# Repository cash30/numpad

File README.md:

<p><b style="font-weight:normal;" id="docs-internal-guid-06ec4c6b-7fff-9c5e-59c2-9c24a0eed1a2"><p dir="ltr" style="line-height:1.425;text-align: center;margin-top:12pt;margin-bottom:12pt;"><span style="font-size:12pt;font-family:Verdana,sans-serif;color:#333333;background-color:#ffffff;font-weight:700;font-style:normal;font-variant:normal;text-decoration:none;vertical-align:baseline;white-space:pre;white-space:pre-wrap;">My Hackpad is just a numpad I'm going to use with the laptop I got from Siege. It's going to have 9 buttons and a rotary encoder for volume.&nbsp;</span></p><p dir="ltr" style="line-height:1.425;text-align: center;margin-top:12pt;margin-bottom:12pt;"><span style="font-size:12pt;font-family:Verdana,sans-serif;color:#333333;background-color:#ffffff;font-weight:700;font-style:normal;font-variant:normal;text-decoration:none;vertical-align:baseline;white-space:pre;white-space:pre-wrap;">Below are pictures of the CAD, schematic, and PCB layout.</span><span style="font-size:12pt;font-family:Verdana,sans-serif;color:#333333;background-color:#ffffff;font-weight:700;font-style:normal;font-variant:normal;text-decoration:none;vertical-align:baseline;white-space:pre;white-space:pre-wrap;"><br></span><span style="font-size:12pt;font-family:Verdana,sans-serif;color:#333333;background-color:#ffffff;font-weight:700;font-style:normal;font-variant:normal;text-decoration:none;vertical-align:baseline;white-space:pre;white-space:pre-wrap;"><br></span><span style="font-size:12pt;font-family:Verdana,sans-serif;color:#333333;background-color:#ffffff;font-weight:700;font-style:normal;font-variant:normal;text-decoration:none;vertical-align:baseline;white-space:pre;white-space:pre-wrap;">I've never made a PCB before so that was neat and i got to actually use CAD for something useful!</span><span style="font-size:12pt;font-family:Verdana,sans-serif;color:#333333;background-color:#ffffff;font-weight:700;font-style:normal;font-variant:normal;text-decoration:none;vertical-align:baseline;white-space:pre;white-space:pre-wrap;"><br></span><span style="font-size:12pt;font-family:Verdana,sans-serif;color:#333333;background-color:#ffffff;font-weight:700;font-style:normal;font-variant:normal;text-decoration:none;vertical-align:baseline;white-space:pre;white-space:pre-wrap;">&nbsp;</span></p><p dir="ltr" style="line-height:1.38;text-align: center;margin-top:0pt;margin-bottom:0pt;"><span style="font-size:12pt;font-family:Verdana,sans-serif;color:#333333;background-color:#ffffff;font-weight:700;font-style:normal;font-variant:normal;text-decoration:none;vertical-align:baseline;white-space:pre;white-space:pre-wrap;"><span style="border:none;display:inline-block;overflow:hidden;width:800px;height:644px;">

<p><strong style="font-weight:normal;" id="docs-internal-guid-06ec4c6b-7fff-9c5e-59c2-9c24a0eed1a2"><span style="font-size:12pt;font-family:Verdana,sans-serif;color:#333333;background-color:#ffffff;font-weight:700;font-style:normal;font-variant:normal;text-decoration:none;vertical-align:baseline;white-space:pre;white-space:pre-wrap;"></span><br></strong></p><p dir="ltr" style="line-height:1.425;text-align: center;margin-top:12pt;margin-bottom:12pt;"><strong style="font-weight:normal;" id="docs-internal-guid-06ec4c6b-7fff-9c5e-59c2-9c24a0eed1a2"><span style="font-size:12pt;font-family:Verdana,sans-serif;color:#333333;background-color:#ffffff;font-weight:700;font-style:normal;font-variant:normal;text-decoration:none;vertical-align:baseline;white-space:pre;white-space:pre-wrap;">BOM:</span></strong></p><ul style="margin-top:0;margin-bottom:0;padding-inline-start:48px;"><li dir="ltr" style="list-style-type:disc;font-size:12pt;font-family:Verdana,sans-serif;color:#333333;background-color:transparent;font-weight:700;font-style:normal;font-variant:normal;text-decoration:none;vertical-align:baseline;white-space:pre;" aria-level="1"><p dir="ltr" style="line-height:1.425;margin-top:12pt;margin-bottom:0pt;" role="presentation"><strong style="font-weight:normal;" id="docs-internal-guid-06ec4c6b-7fff-9c5e-59c2-9c24a0eed1a2"><span style="font-size:12pt;font-family:Verdana,sans-serif;color:#333333;background-color:#ffffff;font-weight:700;font-style:normal;font-variant:normal;text-decoration:none;vertical-align:baseline;white-space:pre;white-space:pre-wrap;">9x Cherry MX red switches</span></strong></p></li><li dir="ltr" style="list-style-type:disc;font-size:12pt;font-family:Verdana,sans-serif;color:#333333;background-color:transparent;font-weight:700;font-style:normal;font-variant:normal;text-decoration:none;vertical-align:baseline;white-space:pre;" aria-level="1"><p dir="ltr" style="line-height:1.425;margin-top:0pt;margin-bottom:0pt;" role="presentation"><strong style="font-weight:normal;" id="docs-internal-guid-06ec4c6b-7fff-9c5e-59c2-9c24a0eed1a2"><span style="font-size:12pt;font-family:Verdana,sans-serif;color:#333333;background-color:#ffffff;font-weight:700;font-style:normal;font-variant:normal;text-decoration:none;vertical-align:baseline;white-space:pre;white-space:pre-wrap;">1x XIAO RP2040</span></strong></p></li><li dir="ltr" style="list-style-type:disc;font-size:12pt;font-family:Verdana,sans-serif;color:#333333;background-color:transparent;font-weight:700;font-style:normal;font-variant:normal;text-decoration:none;vertical-align:baseline;white-space:pre;" aria-level="1"><p dir="ltr" style="line-height:1.425;margin-top:0pt;margin-bottom:0pt;" role="presentation"><strong style="font-weight:normal;" id="docs-internal-guid-06ec4c6b-7fff-9c5e-59c2-9c24a0eed1a2"><span style="font-size:12pt;font-family:Verdana,sans-serif;color:#333333;background-color:#ffffff;font-weight:700;font-style:normal;font-variant:normal;text-decoration:none;vertical-align:baseline;white-space:pre;white-space:pre-wrap;">9x keycaps</span></strong></p></li><li dir="ltr" style="list-style-type:disc;font-size:12pt;font-family:Verdana,sans-serif;color:#333333;background-color:transparent;font-weight:700;font-style:normal;font-variant:normal;text-decoration:none;vertical-align:baseline;white-space:pre;" aria-level="1"><p dir="ltr" style="line-height:1.425;margin-top:0pt;margin-bottom:0pt;" role="presentation"><strong style="font-weight:normal;" id="docs-internal-guid-06ec4c6b-7fff-9c5e-59c2-9c24a0eed1a2"><span style="font-size:12pt;font-family:Verdana,sans-serif;color:#333333;background-color:#ffffff;font-weight:700;font-style:normal;font-variant:normal;text-decoration:none;vertical-align:baseline;white-space:pre;white-space:pre-wrap;">1x 2-sided PCB</span></strong></p></li><li dir="ltr" style="list-style-type:disc;font-size:12pt;font-family:Verdana,sans-serif;color:#333333;background-color:transparent;font-weight:700;font-style:normal;font-variant:normal;text-decoration:none;vertical-align:baseline;white-space:pre;" aria-level="1"><p dir="ltr" style="line-height:1.425;margin-top:0pt;margin-bottom:0pt;" role="presentation"><strong style="font-weight:normal;" id="docs-internal-guid-06ec4c6b-7fff-9c5e-59c2-9c24a0eed1a2"><span style="font-size:12pt;font-family:Verdana,sans-serif;color:#333333;background-color:#ffffff;font-weight:700;font-style:normal;font-variant:normal;text-decoration:none;vertical-align:baseline;white-space:pre;white-space:pre-wrap;">full 3D printed case</span></strong></p></li><li dir="ltr" style="list-style-type:disc;font-size:12pt;font-family:Verdana,sans-serif;color:#333333;background-color:transparent;font-weight:700;font-style:normal;font-variant:normal;text-decoration:none;vertical-align:baseline;white-space:pre;" aria-level="1"><p dir="ltr" style="line-height:1.425;margin-top:0pt;margin-bottom:0pt;" role="presentation"><strong style="font-weight:normal;" id="docs-internal-guid-06ec4c6b-7fff-9c5e-59c2-9c24a0eed1a2"><span style="font-size:12pt;font-family:Verdana,sans-serif;color:#333333;background-color:#ffffff;font-weight:700;font-style:normal;font-variant:normal;text-decoration:none;vertical-align:baseline;white-space:pre;white-space:pre-wrap;">4x M3x16 Bolt</span></strong></p></li><li dir="ltr" style="list-style-type:disc;font-size:12pt;font-family:Verdana,sans-serif;color:#333333;background-color:transparent;font-weight:700;font-style:normal;font-variant:normal;text-decoration:none;vertical-align:baseline;white-space:pre;" aria-level="1"><p dir="ltr" style="line-height:1.425;margin-top:0pt;margin-bottom:12pt;" role="presentation"><strong style="font-weight:normal;" id="docs-internal-guid-06ec4c6b-7fff-9c5e-59c2-9c24a0eed1a2"><span style="font-size:12pt;font-family:Verdana,sans-serif;color:#333333;background-color:#ffffff;font-weight:700;font-style:normal;font-variant:normal;text-decoration:none;vertical-align:baseline;white-space:pre;white-space:pre-wrap;">4x M3 Heatset</span></strong></p></li></ul><p><br></p>

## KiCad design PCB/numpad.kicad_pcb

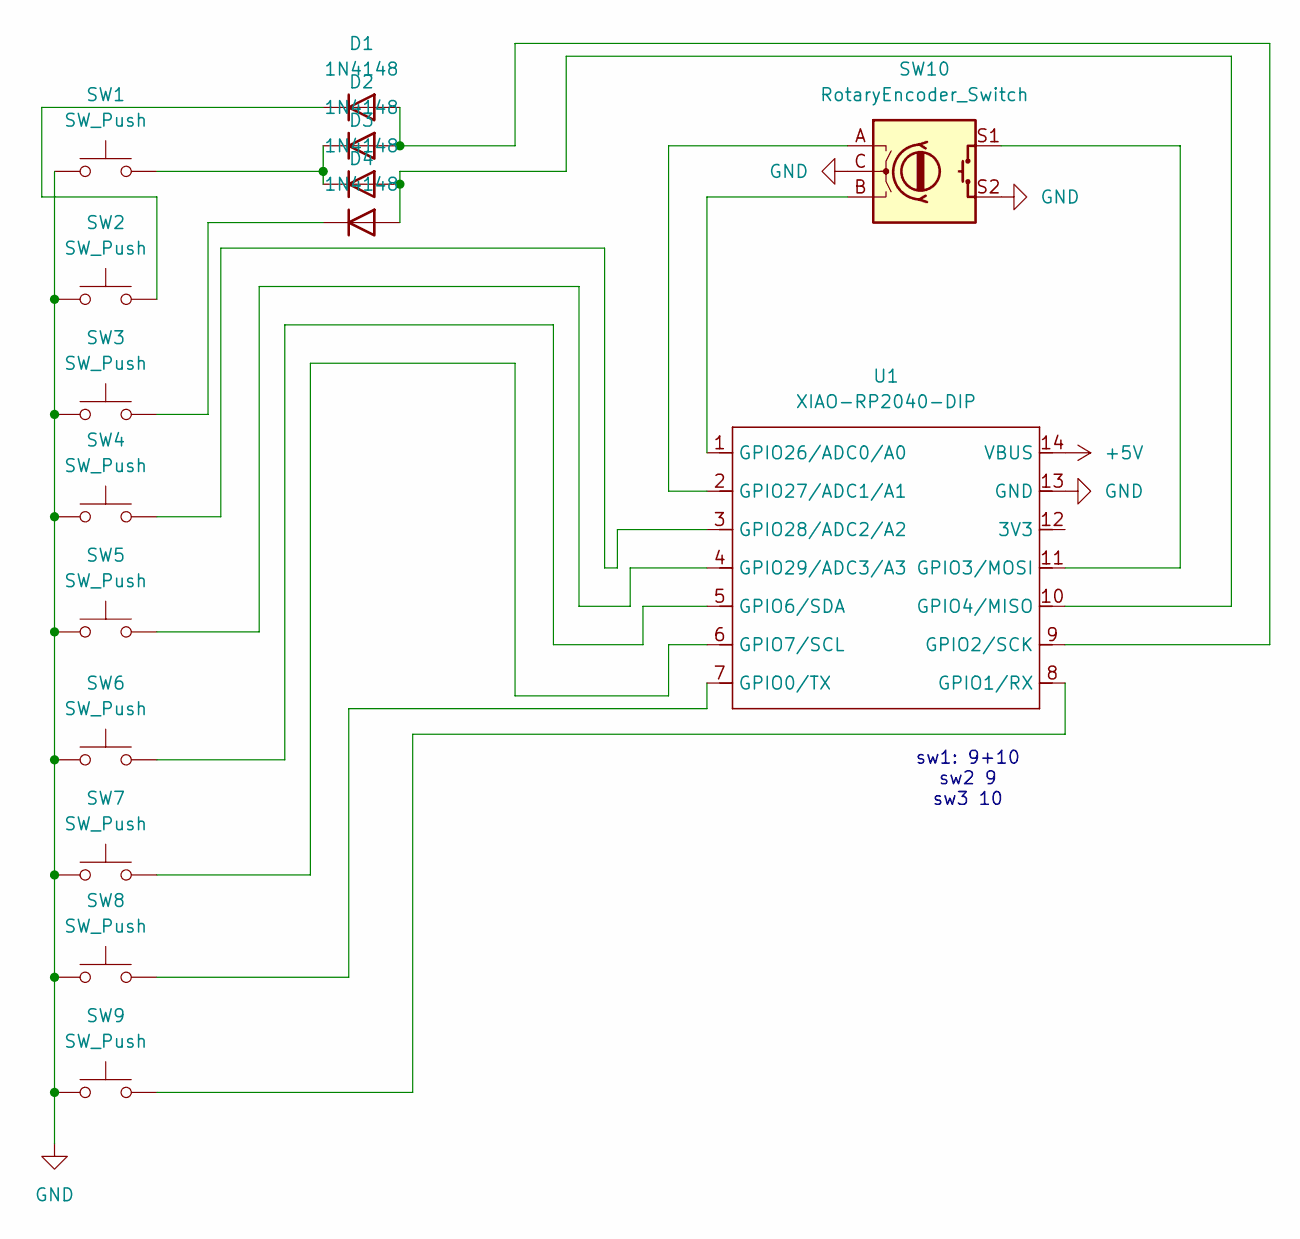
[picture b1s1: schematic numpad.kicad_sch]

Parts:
D1, D2, D3, D4: 1N4148; D_DO-35_SOD27_P7.62mm_Horizontal
SW1, SW2, SW3, SW4, SW5, SW6, SW7, SW8, SW9: SW_Push; SW_Cherry_MX_1.00u_PCB
SW10: RotaryEncoder_Switch; RotaryEncoder_Alps_EC11E-Switch_Vertical_H20mm
U1: XIAO-RP2040-DIP

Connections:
+5V: U1.14 (VBUS)
GND: SW1.1, SW2.1, SW3.1, SW4.1, SW5.1, SW6.1, SW7.1, SW8.1, SW9.1, SW10.C, SW10.S2, U1.13 (GND)
unnamed: D1.2 (A), D2.2 (A), U1.9 (GPIO2/SCK)
unnamed: D1.1 (K), SW2.2
unnamed: D2.1 (K), D3.1 (K), SW1.2
unnamed: D3.2 (A), D4.2 (A), U1.10 (GPIO4/MISO)
unnamed: D4.1 (K), SW3.2
unnamed: SW8.2, U1.7 (GPIO0/TX)
unnamed: SW9.2, U1.8 (GPIO1/RX)
unnamed: SW10.S1, U1.11 (GPIO3/MOSI)
unnamed: SW6.2, U1.5 (GPIO6/SDA)
unnamed: SW7.2, U1.6 (GPIO7/SCL)
unnamed: SW10.B, U1.1 (GPIO26/ADC0/A0)
unnamed: SW10.A, U1.2 (GPIO27/ADC1/A1)
unnamed: SW4.2, U1.3 (GPIO28/ADC2/A2)
unnamed: SW5.2, U1.4 (GPIO29/ADC3/A3)

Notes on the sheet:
sw1: 9+10 sw2 9 sw3 10

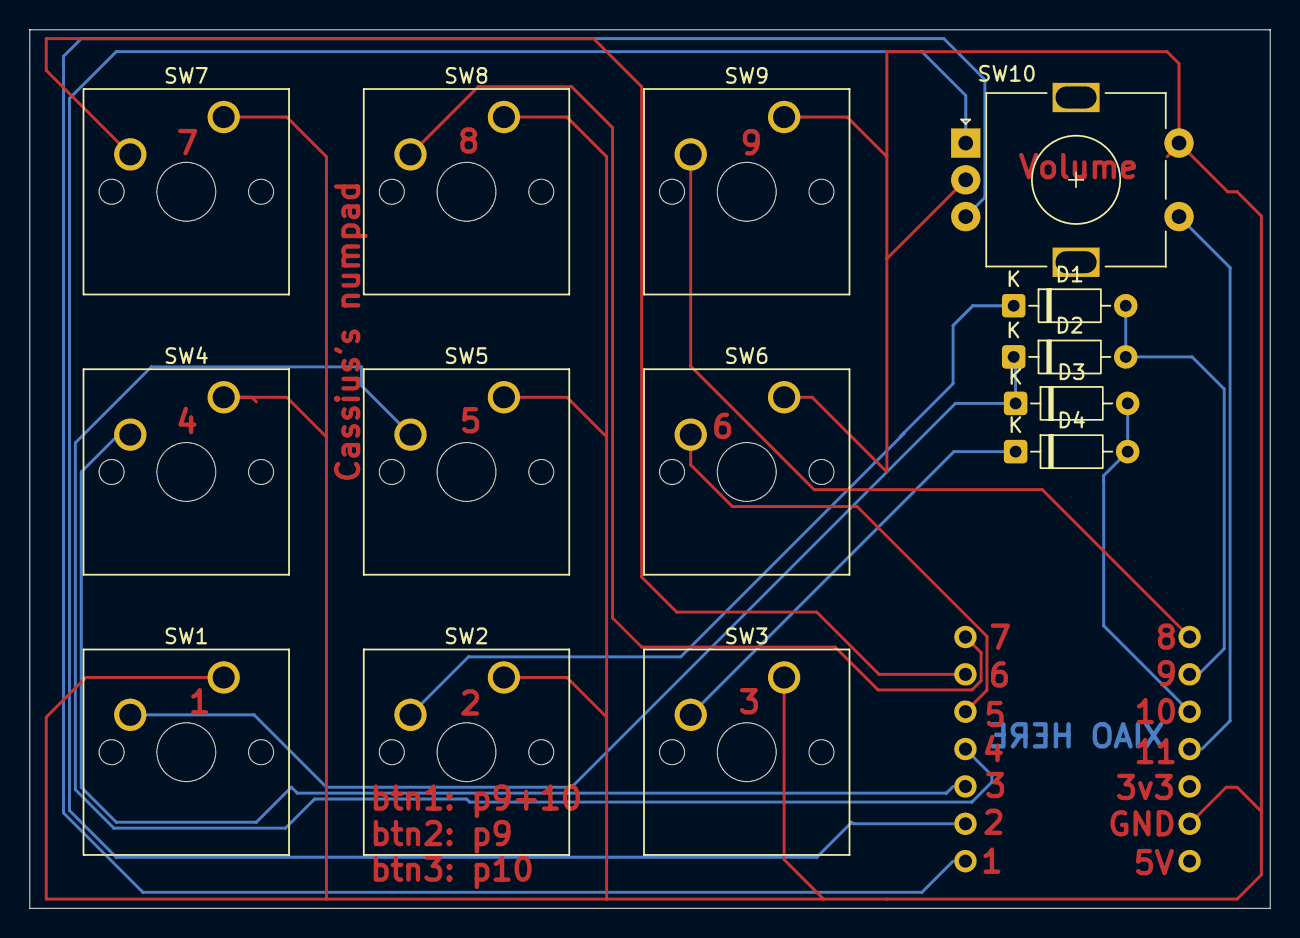
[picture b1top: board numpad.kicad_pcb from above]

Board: 2 copper layers, 84.3 x 59.7 mm, 15 parts (1 on the bottom side), 15 nets.

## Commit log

2025-12-18 first and only commit
2025-12-18 disregard the commit message on the previous commit
2025-12-18 more README stuff
